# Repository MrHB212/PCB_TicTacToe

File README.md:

# PCB_TicTacToe

Ein kleines Projekt um die grundlegenden Schritte von PCB Design kennenzulernen.
Es handelt sich um eine einfache TicTacToe-Schaltung. Vorgesehen waren 9 Schalter,
9 LEDs und 2 verschiedene Spannungsquellen. Einmal per USB-C und ein Terminal.

Die Platine wurde bestellt und ist angekommen, allerdings waren da Fehler enthalten:
- Footprint für Schalter zu klein
- LED THT waren zu nah dran zum selbstlöten, potentielle Kurzschlüsse
- Manche Leitungen scheinen nicht zu stimmen

Infolgedessen konnte ich es nicht zusammenbauen und ausprobieren.

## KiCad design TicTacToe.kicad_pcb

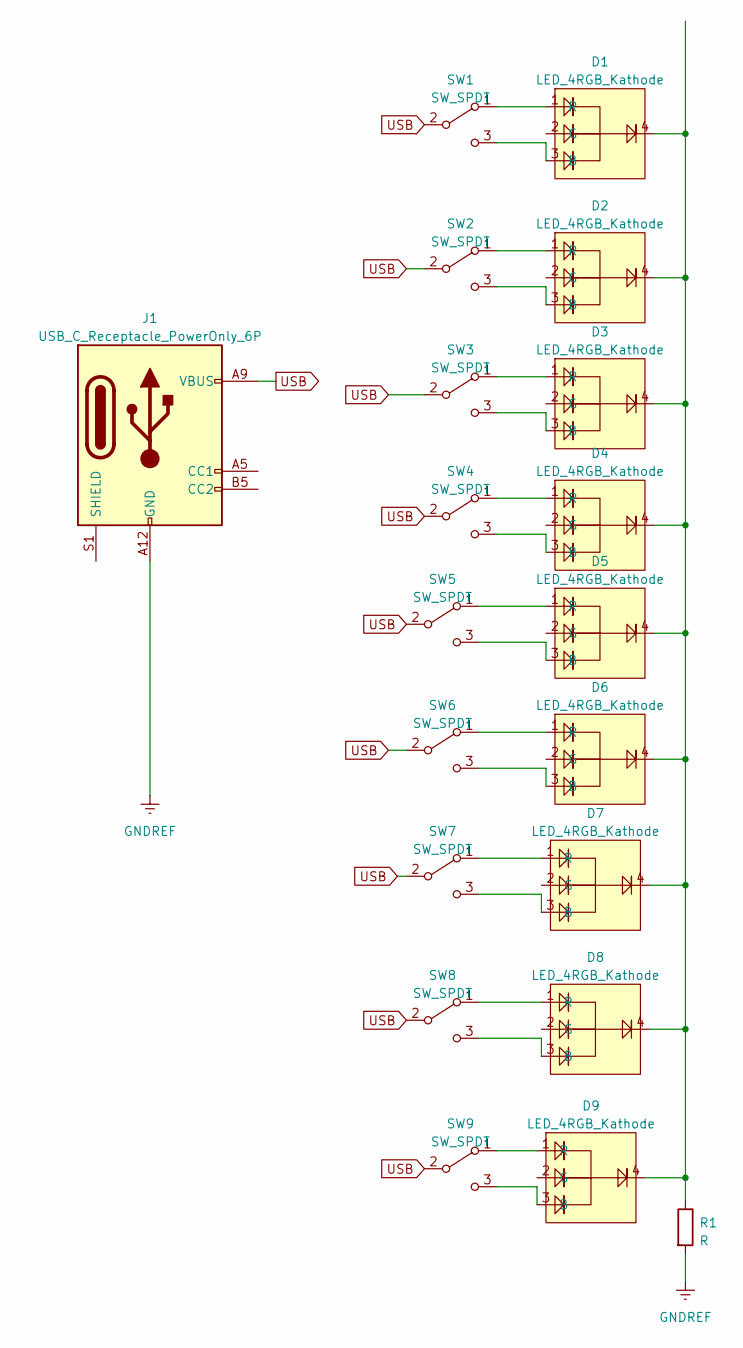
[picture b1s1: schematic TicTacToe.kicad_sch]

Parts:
D1, D2, D3, D4, D5, D6, D7, D8, D9: LED_4RGB_Kathode
J1: USB_C_Receptacle_PowerOnly_6P; USB_C_6P_PowerOnly
R1: R; R_Axial_DIN0204_L3.6mm_D1.6mm_P5.08mm_Horizontal
SW1, SW2, SW3, SW4, SW5, SW6, SW7, SW8, SW9: SW_SPDT; Kippschalter_3P_3Pins

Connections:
GNDREF: J1.A12 (GND), J1.B12 (GND), R1.2
unnamed: D1.3 (B), SW1.3 (C)
unnamed: D1.4, D2.4, D3.4, D4.4, D5.4, D6.4, D7.4, D8.4, D9.4, R1.1
unnamed: D1.1 (R), SW1.1 (A)
unnamed: D2.3 (B), SW2.3 (C)
unnamed: D2.1 (R), SW2.1 (A)
unnamed: D3.3 (B), SW3.3 (C)
unnamed: D3.1 (R), SW3.1 (A)
unnamed: D4.3 (B), SW4.3 (C)
unnamed: D4.1 (R), SW4.1 (A)
unnamed: D5.3 (B), SW5.3 (C)
unnamed: D5.1 (R), SW5.1 (A)
unnamed: D6.3 (B), SW6.3 (C)
unnamed: D6.1 (R), SW6.1 (A)
unnamed: D7.3 (B), SW7.3 (C)
unnamed: D7.1 (R), SW7.1 (A)
unnamed: D8.3 (B), SW8.3 (C)
unnamed: D8.1 (R), SW8.1 (A)
unnamed: D9.3 (B), SW9.3 (C)
unnamed: D9.1 (R), SW9.1 (A)
USB: J1.A9 (VBUS), J1.B9 (VBUS), SW1.2 (B), SW2.2 (B), SW3.2 (B), SW4.2 (B), SW5.2 (B), SW6.2 (B), SW7.2 (B), SW8.2 (B), SW9.2 (B)

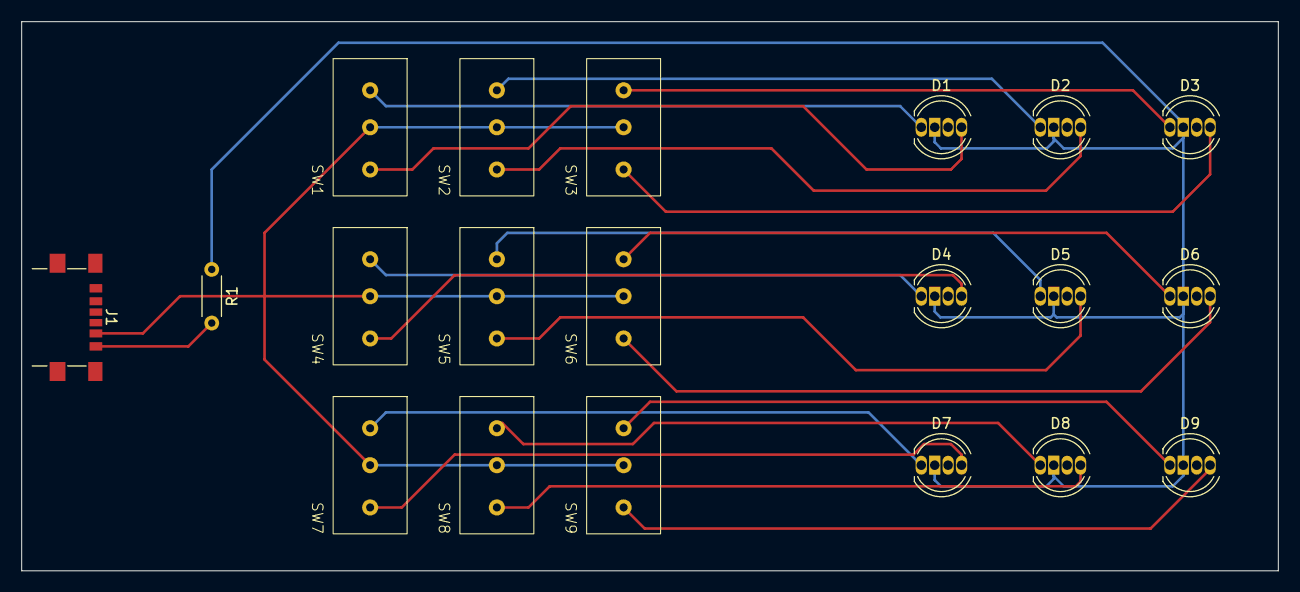
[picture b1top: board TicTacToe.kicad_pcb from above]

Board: 2 copper layers, 119.0 x 52.0 mm, 20 parts (0 on the bottom side), 21 nets.

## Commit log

2025-01-24 Projektdaten hinzugefügt
